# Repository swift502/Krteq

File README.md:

# Krteq

An extended 5x12 keyboard with 2 extra keys. Intended for ortho layouts with a shifted number row, allowing for the placement of the delete and tilde keys above their usual spots.

Krteq is a successor to [Krtkus](https://github.com/swift502/Krtkus), learning from its lessons to make a design that's better encapsulated and much more complete.

### Features

- Low profile
- Hotswap
- RGB backlight
- QMK/VIA compatible
- 3D printed case with a 7 degree tilt
- Tray mount
- 233mm × 121mm × 30mm

Connecting the keyboard to [usevia.app](https://usevia.app) requires manually uploading the [design file](production/krteq_via.json) in the design tab.

## Build guide

### Parts

- [PCB](#pcb)
- [Case](#case)
- Keycaps
- 61x Gateron KS-33 switch
- Gateron 2u low profile plate-mounted stabilizer

<!-- -->

- Raspberry Pi Pico
- USB-C breakout board
- OLED display module

<!-- -->

- 11x connecting wire
- 8x 2,2x8mm thread-forming screws for plastic
- Rubber feet

### Breakout boards

The **USB-C breakout board** is expected to match the specs of the Adafruit USB-C breakout board with two M2.5 screw holes 15.24mm apart, 2.54mm from the front edge, and built-in resistors for the CC lines.

The **OLED display module** is expected to be a 128x32 I2C OLED screen. These screens are not very standardized, so the PCB cutout is generous to fit modules with slightly different dimensions. Any OLED roughly equal or less than 38x12mm should fit, and at most require slight modifications to the display cutout in the plate.

### Assembly

1. Perform the initial firmware flash on the Pico
1. Attach the stabilizer to the plate
1. Place the OLED module into plate's display slot
1. Screw the USB board to the plate
1. Solder the Pico onto the PCB
1. Secure the plate to the PCB by installing few of the switches
1. Cut up wire lenghts:
    - 8x 15mm
    - 2x 18mm (TP2, TP3)
    - 1x 22mm (TP1)
1. Solder the wires to the PCB and the components 
1. Screw the plate to the case
1. Install the rest of the switches, put some keycaps on and you're done!

## PCB

The Kicad 10 project can be found in [source/kicad](source/kicad). All parts are SMD, the PCB is intended to be ordered with pre-assembled SMD components for an easier, although more expensive build process.

To generate fabrication files, open the Kicad project and use an export plugin provided by the PCB manufacturer you want to order from. The order process is then highly dependent on the manufacturer.

### Suggested BOM

| Part | Package | Manufacturer Part Number |
|---|---|---|
| Switch diode | SOD-123 | 1N4148W |
| Switch socket | SMD | KS-2P02B01-02 |
| RGB LED | SMD-4P,3.2x1.3mm | 23-23B/R6GHBHC-A30/2A |
| RGB driver | QFN-48-EP(6x6) | IS31FL3733B-QFLS4-TR |
| 0.1µF capacitor | 0402 | CL05B104KO5NNNC |
| 0.47µF capacitor | 0603 | CL10B474KA8NNNC |
| 22µF/10V capacitor | CASE-A-3216-18(mm) | T520A226M010ATE080 |
| 2kΩ resistor | 0603 | 0603WAF2001T5E |
| 20kΩ resistor | 0603 | 0603WAF2002T5E |
| 100kΩ resistor | 0603 | 0603WAF1003T5E |

## Case

Case blend file can be found in [source/Krteq.blend](source/Krteq.blend). It's designed non-destructively, so it should be easy to modify if needed.

STL files for 3D printing can be found in [production/stl](production/stl). Recommended printing parameters are:

- PLA
- 0.15mm layer height
- 100% infill

The plate also has a "keychron" variant, which adjusts stabilizer cutouts for their non-standard [triangular stem design](https://www.keychron.com/blogs/news/the-design-details-of-our-keychron-low-profile-keyboard-stabilizers).

## Firmware

QMK/VIA setup with a few custom features:

- custom keycodes for volume, screen and RGB control
- pressing <kbd>LShift</kbd> + <kbd>RShift</kbd> + <kbd>Space</kbd> enters bootloader mode
- pressing <kbd>LShift</kbd> + <kbd>RShift</kbd> + <kbd>Delete</kbd> reverts to the default keymap

### Overrides

Some functionality can be overridden in a user keymap `config.h`:

```c
// Replace the scroll lock indicator with three letter
// string to denote custom script functionality
#define INDICATORS_SCROLL_LABEL "ACC"

// Layer which forces a preview of the "Indicators" screen
#define INDICATORS_SHOW_LAYER 1

// Layer (and above) which shows the "Input lock" screen
#define INPUT_LOCK_LAYER 4

```

### Adding custom OLED screens

In QMK, user keymaps can completely override oled rendering via `oled_task_user()`. However, Krteq also exposes its custom screen system, where screen interaction is done via the `KRT_SCR` keycode. Hooking into this system is preferred as it ensures that other built-in system screen features continue to work properly.

Here's a minimal example of a custom screen definition in a user keymap:

```c
// 1. Create a render function
static void custom_screen_render(void)
{
    oled_write_P(PSTR("Hello world"), false);
}

// 2. Construct a screen instance
static const krteq_screen_t custom_screen = {
    .name = "Custom screen",
    .start = custom_screen_render,
};

// 3. Override built-in screen list
const krteq_screen_t *const user_screens[] = {
    &custom_screen
};
```

Here's a table of fields and callbacks available for screens to implement:

| Property     | Description |
| ------------ | ----------- |
| `.name`      | Display name string |
| `.init`      | Runs once on keyboard start-up |
| `.start`     | Runs every time the screen is activated |
| `.update`    | Runs every OLED task cycle when screen is active |
| `.key_event` | Key press event |

You can combine custom screens with the built-in ones. You can reshuffle them, remove some and add your own. The built-in screen list goes as follows:

```c
const krteq_screen_t *const user_screens[] = {
    &krteq_screen_indicators,
    &krteq_screen_bongo_cat,
    &krteq_screen_starfield,
    &krteq_screen_matrix,
    &krteq_screen_waves,
    &krteq_screen_game_of_life,
    &krteq_screen_system_info
};
```

### Compiling (Windows)

Install:

- Python: https://www.python.org/
- MSYS: https://msys.qmk.fm

Run the compile script:

```sh
python source/scripts/qmk_compile.py
```

### Flashing (Windows)

For the initial flash, hold the BOOTSEL button while connecting the Pico to a computer to have it show up as a storage device, then copy the compiled [firmware file](production/krteq_firmware.uf2) over to it.

Once flashed, you can trigger the bootloader mode again by simply pressing the <kbd>LShift</kbd> + <kbd>RShift</kbd> + <kbd>Space</kbd> key combination.

## Documentation

### QMK

- Info.json: https://docs.qmk.fm/reference_info_json
- Keycodes: https://docs.qmk.fm/keycodes
- Default keymap: https://docs.qmk.fm/configurator_default_keymaps
- RGB matrix: https://docs.qmk.fm/features/rgb_matrix
- OLED: https://docs.qmk.fm/features/oled_driver

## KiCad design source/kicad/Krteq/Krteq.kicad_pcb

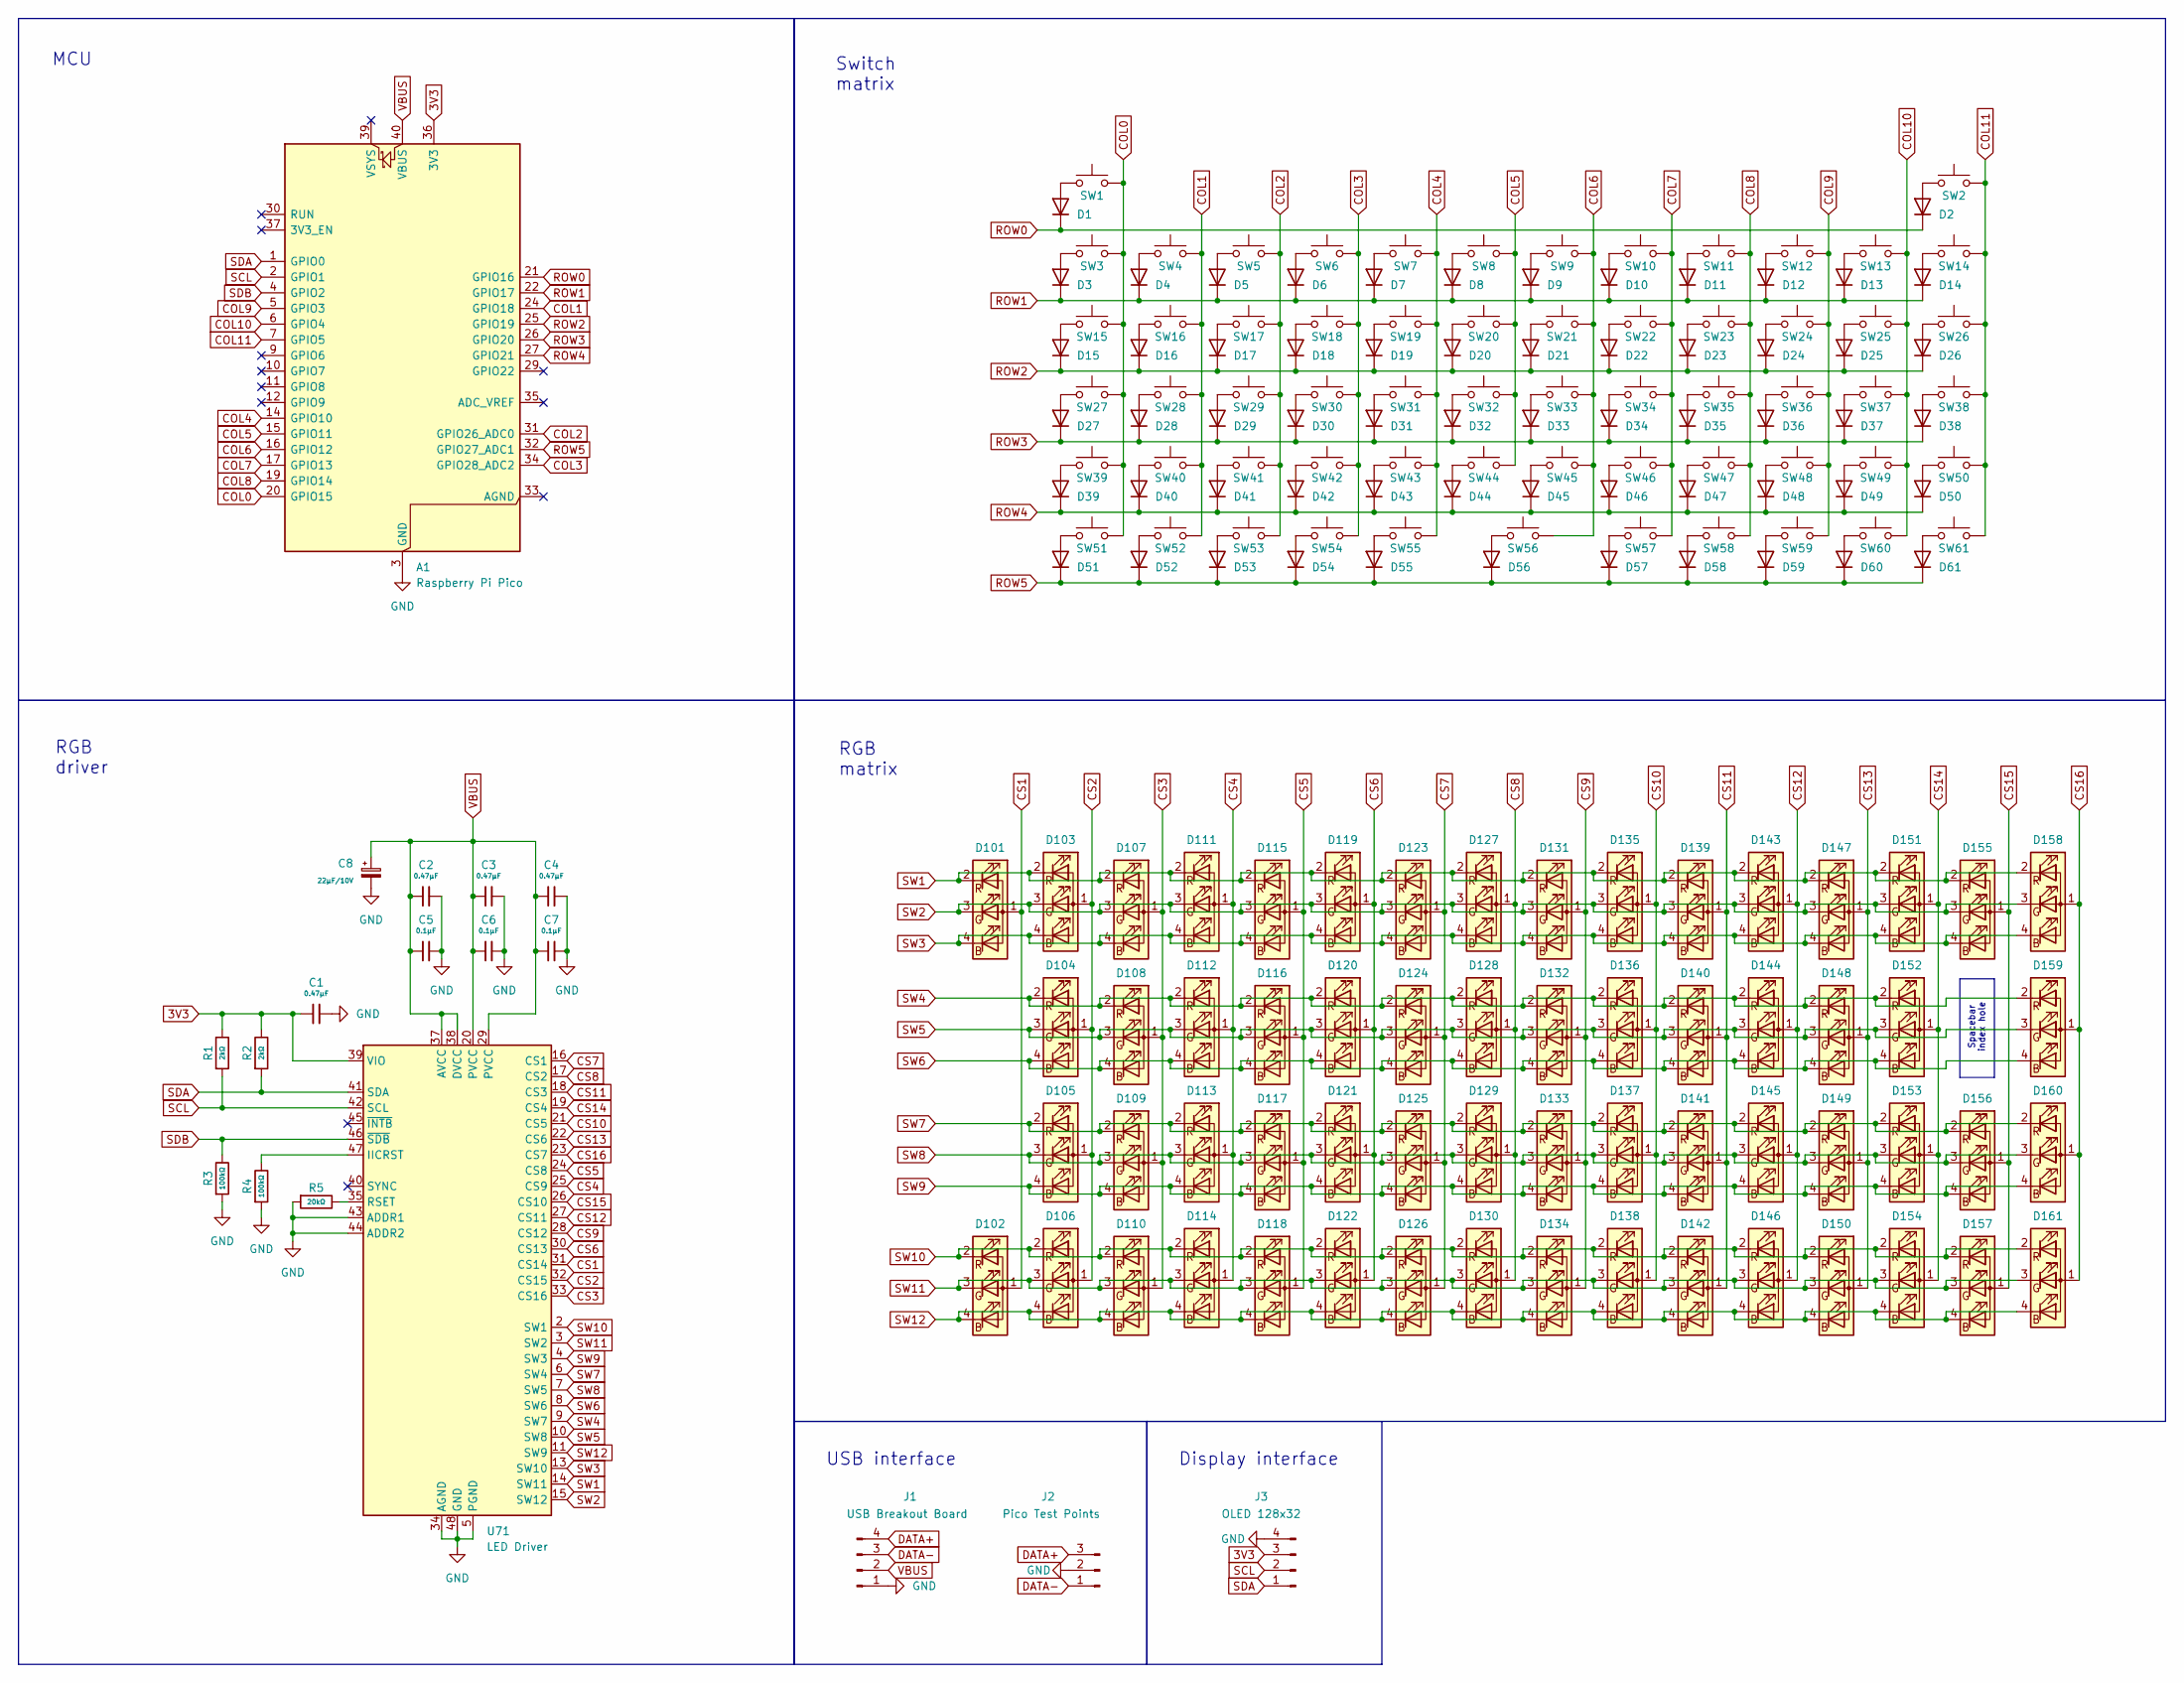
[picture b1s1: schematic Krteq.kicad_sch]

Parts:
A1: Raspberry Pi Pico; RaspberryPi_Pico
C1, C2, C3, C4: 0.47µF; C_0603_1608Metric; MPN CL10B474KA8NNNC
C5, C6, C7: 0.1µF; C_0402_1005Metric; MPN CL05B104KO5NNNC
C8: 22µF/10V; CASE-A-3216-18(mm); MPN T520A226M010ATE080
D1, D2, D3, D4, D5, D6, D7, D8, D9, D10, D11, D12, D13, D14, D15, D16, D17, D18, D19, D20, D21, D22, D23, D24, D25, D26, D27, D28, D29, D30, D31, D32, D33, D34, D35, D36, D37, D38, D39, D40, D41, D42, D43, D44, D45, D46, D47, D48, D49, D50, D51, D52, D53, D54, D55, D56, D57, D58, D59, D60, D61: Switch Diode; D_SOD-123; MPN 1N4148W
D101, D102, D103, D104, D105, D106, D107, D108, D109, D110, D111, D112, D113, D114, D115, D116, D117, D118, D119, D120, D121, D122, D123, D124, D125, D126, D127, D128, D129, D130, D131, D132, D133, D134, D135, D136, D137, D138, D139, D140, D141, D142, D143, D144, D145, D146, D147, D148, D149, D150, D151, D152, D153, D154, D155, D156, D157, D158, D159, D160, D161: Reverse Mount LED ARGB; SMD-4P_3.2x1.3mm; MPN 23-23B/R6GHBHC-A30/2A
J1: USB Breakout Board; Interface_1x04_P2.54mm
J2: Pico Test Points; Interface_1x03_P2.54mm
J3: OLED 128x32; Interface_1x04_P2.54mm
R1, R2: 2kΩ; R_0603_1608Metric; MPN 0603WAF2001T5E
R3, R4: 100kΩ; R_0603_1608Metric; MPN 0603WAF1003T5E
R5: 20kΩ; R_0603_1608Metric; MPN 0603WAF2002T5E
SW1, SW2, SW3, SW4, SW5, SW6, SW7, SW8, SW9, SW10, SW11, SW12, SW13, SW14, SW15, SW16, SW17, SW18, SW19, SW20, SW21, SW22, SW23, SW24, SW25, SW26, SW27, SW28, SW29, SW30, SW31, SW32, SW33, SW34, SW35, SW36, SW37, SW38, SW39, SW40, SW41, SW42, SW43, SW44, SW45, SW46, SW47, SW48, SW49, SW50, SW51, SW52, SW53, SW54, SW55, SW56, SW57, SW58, SW59, SW60, SW61: GATERON Low Profile Switch Hot-swap Socket; Gateron_KS-33; MPN KS-2P02B01-02
U71: LED Driver; QFN-48_6x6mm; MPN IS31FL3733B-QFLS4-TR

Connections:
3V3: A1.36 (3V3), C1.1, J3.3, R1.1, R2.1, U71.39 (VIO)
COL0: A1.20 (GPIO15), SW1.2, SW3.2, SW15.2, SW27.2, SW39.2, SW51.2
COL1: A1.24 (GPIO18), SW4.2, SW16.2, SW28.2, SW40.2, SW52.2
COL2: A1.31 (GPIO26_ADC0), SW5.2, SW17.2, SW29.2, SW41.2, SW53.2
COL3: A1.34 (GPIO28_ADC2), SW6.2, SW18.2, SW30.2, SW42.2, SW54.2
COL4: A1.14 (GPIO10), SW7.2, SW19.2, SW31.2, SW43.2, SW55.2
COL5: A1.15 (GPIO11), SW8.2, SW20.2, SW32.2, SW44.2
COL6: A1.16 (GPIO12), SW9.2, SW21.2, SW33.2, SW45.2, SW56.2
COL7: A1.17 (GPIO13), SW10.2, SW22.2, SW34.2, SW46.2, SW57.2
COL8: A1.19 (GPIO14), SW11.2, SW23.2, SW35.2, SW47.2, SW58.2
COL9: A1.5 (GPIO3), SW12.2, SW24.2, SW36.2, SW48.2, SW59.2
COL10: A1.6 (GPIO4), SW13.2, SW25.2, SW37.2, SW49.2, SW60.2
COL11: A1.7 (GPIO5), SW2.2, SW14.2, SW26.2, SW38.2, SW50.2, SW61.2
CS1: D101.1 (A), D102.1 (A), U71.31 (CS14)
CS2: D103.1 (A), D104.1 (A), D105.1 (A), D106.1 (A), U71.32 (CS15)
CS3: D107.1 (A), D108.1 (A), D109.1 (A), D110.1 (A), U71.33 (CS16)
CS4: D111.1 (A), D112.1 (A), D113.1 (A), D114.1 (A), U71.25 (CS9)
CS5: D115.1 (A), D116.1 (A), D117.1 (A), D118.1 (A), U71.24 (CS8)
CS6: D119.1 (A), D120.1 (A), D121.1 (A), D122.1 (A), U71.30 (CS13)
CS7: D123.1 (A), D124.1 (A), D125.1 (A), D126.1 (A), U71.16 (CS1)
CS8: D127.1 (A), D128.1 (A), D129.1 (A), D130.1 (A), U71.17 (CS2)
CS9: D131.1 (A), D132.1 (A), D133.1 (A), D134.1 (A), U71.28 (CS12)
CS10: D135.1 (A), D136.1 (A), D137.1 (A), D138.1 (A), U71.21 (CS5)
CS11: D139.1 (A), D140.1 (A), D141.1 (A), D142.1 (A), U71.18 (CS3)
CS12: D143.1 (A), D144.1 (A), D145.1 (A), D146.1 (A), U71.27 (CS11)
CS13: D147.1 (A), D148.1 (A), D149.1 (A), D150.1 (A), U71.22 (CS6)
CS14: D151.1 (A), D152.1 (A), D153.1 (A), D154.1 (A), U71.19 (CS4)
CS15: D155.1 (A), D156.1 (A), D157.1 (A), U71.26 (CS10)
CS16: D158.1 (A), D159.1 (A), D160.1 (A), D161.1 (A), U71.23 (CS7)
DATA+: J1.4, J2.3
DATA-: J1.3, J2.1
GND: A1.3 (GND), A1.8 (GND), A1.13 (GND), A1.18 (GND), A1.23 (GND), A1.28 (GND), A1.38 (GND), C1.2, C2.2, C3.2, C4.2, C5.2, C6.2, C7.2, C8.2, J1.1, J2.2, J3.4, R3.2, R4.2, R5.2, U71.5 (PGND), U71.12 (PGND), U71.34 (AGND), U71.43 (ADDR1), U71.44 (ADDR2), U71.48 (GND), U71.49 (GND)
unnamed: D1.2 (A), SW1.1
unnamed: D2.2 (A), SW2.1
unnamed: D3.2 (A), SW3.1
unnamed: D4.2 (A), SW4.1
unnamed: D5.2 (A), SW5.1
unnamed: D6.2 (A), SW6.1
unnamed: D7.2 (A), SW7.1
unnamed: D8.2 (A), SW8.1
unnamed: D9.2 (A), SW9.1
unnamed: D10.2 (A), SW10.1
unnamed: D11.2 (A), SW11.1
unnamed: D12.2 (A), SW12.1
unnamed: D13.2 (A), SW13.1
unnamed: D14.2 (A), SW14.1
unnamed: D15.2 (A), SW15.1
unnamed: D16.2 (A), SW16.1
unnamed: D17.2 (A), SW17.1
unnamed: D18.2 (A), SW18.1
unnamed: D19.2 (A), SW19.1
unnamed: D20.2 (A), SW20.1
unnamed: D21.2 (A), SW21.1
unnamed: D22.2 (A), SW22.1
unnamed: D23.2 (A), SW23.1
unnamed: D24.2 (A), SW24.1
unnamed: D25.2 (A), SW25.1
unnamed: D26.2 (A), SW26.1
unnamed: D27.2 (A), SW27.1
unnamed: D28.2 (A), SW28.1
unnamed: D29.2 (A), SW29.1
unnamed: D30.2 (A), SW30.1
unnamed: D31.2 (A), SW31.1
unnamed: D32.2 (A), SW32.1
unnamed: D33.2 (A), SW33.1
unnamed: D34.2 (A), SW34.1
unnamed: D35.2 (A), SW35.1
unnamed: D36.2 (A), SW36.1
unnamed: D37.2 (A), SW37.1
unnamed: D38.2 (A), SW38.1
unnamed: D39.2 (A), SW39.1
unnamed: D40.2 (A), SW40.1
unnamed: D41.2 (A), SW41.1
unnamed: D42.2 (A), SW42.1
unnamed: D43.2 (A), SW43.1
unnamed: D44.2 (A), SW44.1
unnamed: D45.2 (A), SW45.1
unnamed: D46.2 (A), SW46.1
unnamed: D47.2 (A), SW47.1
unnamed: D48.2 (A), SW48.1
unnamed: D49.2 (A), SW49.1
unnamed: D50.2 (A), SW50.1
unnamed: D51.2 (A), SW51.1
unnamed: D52.2 (A), SW52.1
unnamed: D53.2 (A), SW53.1
unnamed: D54.2 (A), SW54.1
unnamed: D55.2 (A), SW55.1
unnamed: D56.2 (A), SW56.1
unnamed: D57.2 (A), SW57.1
unnamed: D58.2 (A), SW58.1
unnamed: D59.2 (A), SW59.1
unnamed: D60.2 (A), SW60.1
unnamed: D61.2 (A), SW61.1
unnamed: R4.1, U71.47 (IICRST)
unnamed: R5.1, U71.35 (RSET)
ROW0: A1.21 (GPIO16), D1.1 (K), D2.1 (K)
ROW1: A1.22 (GPIO17), D3.1 (K), D4.1 (K), D5.1 (K), D6.1 (K), D7.1 (K), D8.1 (K), D9.1 (K), D10.1 (K), D11.1 (K), D12.1 (K), D13.1 (K), D14.1 (K)
ROW2: A1.25 (GPIO19), D15.1 (K), D16.1 (K), D17.1 (K), D18.1 (K), D19.1 (K), D20.1 (K), D21.1 (K), D22.1 (K), D23.1 (K), D24.1 (K), D25.1 (K), D26.1 (K)
ROW3: A1.26 (GPIO20), D27.1 (K), D28.1 (K), D29.1 (K), D30.1 (K), D31.1 (K), D32.1 (K), D33.1 (K), D34.1 (K), D35.1 (K), D36.1 (K), D37.1 (K), D38.1 (K)
ROW4: A1.27 (GPIO21), D39.1 (K), D40.1 (K), D41.1 (K), D42.1 (K), D43.1 (K), D44.1 (K), D45.1 (K), D46.1 (K), D47.1 (K), D48.1 (K), D49.1 (K), D50.1 (K)
ROW5: A1.32 (GPIO27_ADC1), D51.1 (K), D52.1 (K), D53.1 (K), D54.1 (K), D55.1 (K), D56.1 (K), D57.1 (K), D58.1 (K), D59.1 (K), D60.1 (K), D61.1 (K)
SCL: A1.2 (GPIO1), J3.2, R1.2, U71.42 (SCL)
SDA: A1.1 (GPIO0), J3.1, R2.2, U71.41 (SDA)
SDB: A1.4 (GPIO2), R3.1, U71.46 (~SDB)
SW1: D101.2 (RK), D103.2 (RK), D107.2 (RK), D111.2 (RK), D115.2 (RK), D119.2 (RK), D123.2 (RK), D127.2 (RK), D131.2 (RK), D135.2 (RK), D139.2 (RK), D143.2 (RK), D147.2 (RK), D151.2 (RK), D155.2 (RK), D158.2 (RK), U71.14 (SW11)
SW2: D101.3 (GK), D103.3 (GK), D107.3 (GK), D111.3 (GK), D115.3 (GK), D119.3 (GK), D123.3 (GK), D127.3 (GK), D131.3 (GK), D135.3 (GK), D139.3 (GK), D143.3 (GK), D147.3 (GK), D151.3 (GK), D155.3 (GK), D158.3 (GK), U71.15 (SW12)
SW3: D101.4 (BK), D103.4 (BK), D107.4 (BK), D111.4 (BK), D115.4 (BK), D119.4 (BK), D123.4 (BK), D127.4 (BK), D131.4 (BK), D135.4 (BK), D139.4 (BK), D143.4 (BK), D147.4 (BK), D151.4 (BK), D155.4 (BK), D158.4 (BK), U71.13 (SW10)
SW4: D104.2 (RK), D108.2 (RK), D112.2 (RK), D116.2 (RK), D120.2 (RK), D124.2 (RK), D128.2 (RK), D132.2 (RK), D136.2 (RK), D140.2 (RK), D144.2 (RK), D148.2 (RK), D152.2 (RK), D159.2 (RK), U71.9 (SW7)
SW5: D104.3 (GK), D108.3 (GK), D112.3 (GK), D116.3 (GK), D120.3 (GK), D124.3 (GK), D128.3 (GK), D132.3 (GK), D136.3 (GK), D140.3 (GK), D144.3 (GK), D148.3 (GK), D152.3 (GK), D159.3 (GK), U71.10 (SW8)
SW6: D104.4 (BK), D108.4 (BK), D112.4 (BK), D116.4 (BK), D120.4 (BK), D124.4 (BK), D128.4 (BK), D132.4 (BK), D136.4 (BK), D140.4 (BK), D144.4 (BK), D148.4 (BK), D152.4 (BK), D159.4 (BK), U71.8 (SW6)
SW7: D105.2 (RK), D109.2 (RK), D113.2 (RK), D117.2 (RK), D121.2 (RK), D125.2 (RK), D129.2 (RK), D133.2 (RK), D137.2 (RK), D141.2 (RK), D145.2 (RK), D149.2 (RK), D153.2 (RK), D156.2 (RK), D160.2 (RK), U71.6 (SW4)
SW8: D105.3 (GK), D109.3 (GK), D113.3 (GK), D117.3 (GK), D121.3 (GK), D125.3 (GK), D129.3 (GK), D133.3 (GK), D137.3 (GK), D141.3 (GK), D145.3 (GK), D149.3 (GK), D153.3 (GK), D156.3 (GK), D160.3 (GK), U71.7 (SW5)
SW9: D105.4 (BK), D109.4 (BK), D113.4 (BK), D117.4 (BK), D121.4 (BK), D125.4 (BK), D129.4 (BK), D133.4 (BK), D137.4 (BK), D141.4 (BK), D145.4 (BK), D149.4 (BK), D153.4 (BK), D156.4 (BK), D160.4 (BK), U71.4 (SW3)
SW10: D102.2 (RK), D106.2 (RK), D110.2 (RK), D114.2 (RK), D118.2 (RK), D122.2 (RK), D126.2 (RK), D130.2 (RK), D134.2 (RK), D138.2 (RK), D142.2 (RK), D146.2 (RK), D150.2 (RK), D154.2 (RK), D157.2 (RK), D161.2 (RK), U71.2 (SW1)
SW11: D102.3 (GK), D106.3 (GK), D110.3 (GK), D114.3 (GK), D118.3 (GK), D122.3 (GK), D126.3 (GK), D130.3 (GK), D134.3 (GK), D138.3 (GK), D142.3 (GK), D146.3 (GK), D150.3 (GK), D154.3 (GK), D157.3 (GK), D161.3 (GK), U71.3 (SW2)
SW12: D102.4 (BK), D106.4 (BK), D110.4 (BK), D114.4 (BK), D118.4 (BK), D122.4 (BK), D126.4 (BK), D130.4 (BK), D134.4 (BK), D138.4 (BK), D142.4 (BK), D146.4 (BK), D150.4 (BK), D154.4 (BK), D157.4 (BK), D161.4 (BK), U71.11 (SW9)
VBUS: A1.40 (VBUS), C2.1, C3.1, C4.1, C5.1, C6.1, C7.1, C8.1, J1.2, U71.20 (PVCC), U71.29 (PVCC), U71.37 (AVCC), U71.38 (DVCC)

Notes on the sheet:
RGB matrix
Switch matrix
RGB driver
USB interface
Spacebar index hole
MCU
Display interface

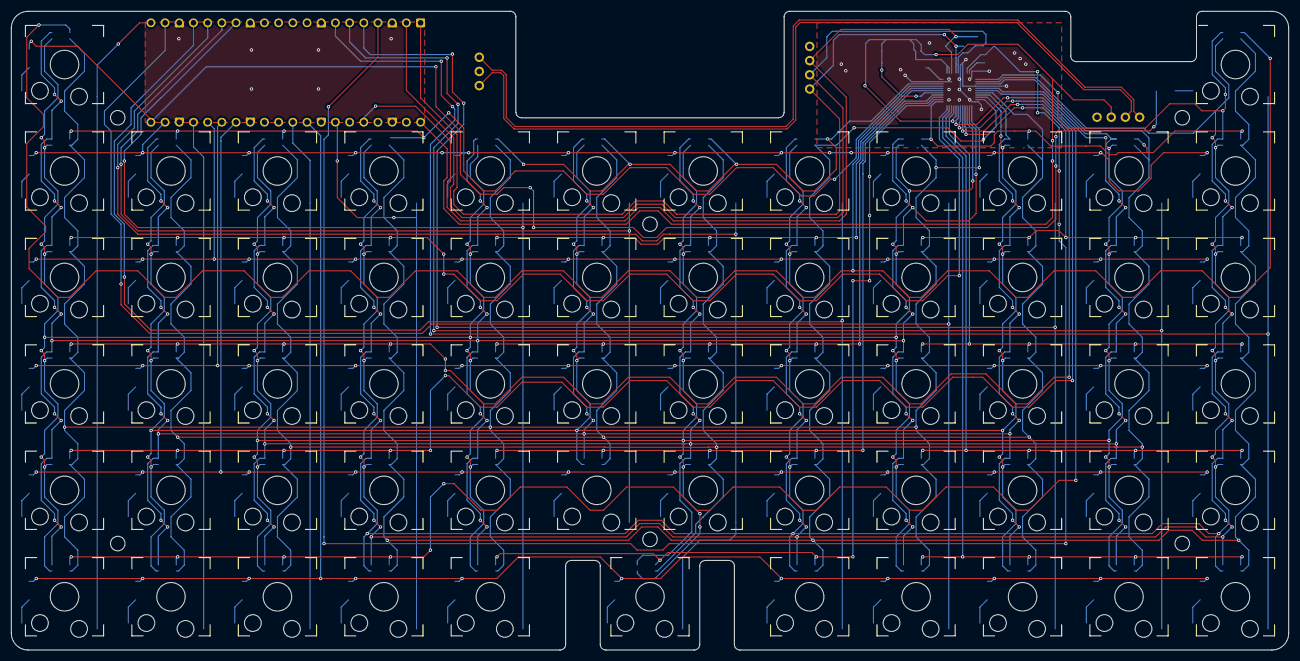
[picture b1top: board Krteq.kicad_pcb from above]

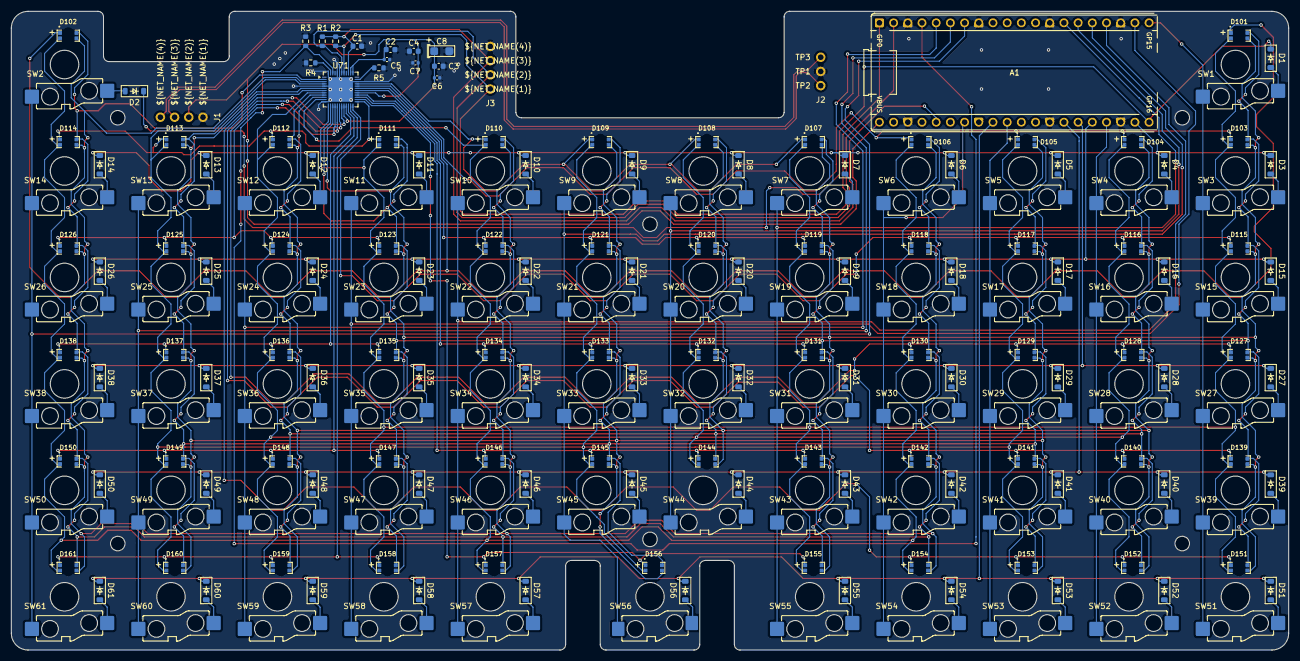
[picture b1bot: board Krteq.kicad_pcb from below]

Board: 2 copper layers, 228.6 x 114.3 mm, 201 parts (201 on the bottom side), 117 nets.

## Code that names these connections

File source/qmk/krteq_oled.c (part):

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
// Drawn as rows top to bottom, 3 bits each, the leftmost pixel in the highest bit
// Stored as columns left to right, 4 bits each, the top pixel in the lowest bit, which the frame buffer takes directly
#define RAIN_GLYPH_COLUMN(row0, row1, row2, row3, bit) \
    (((row0) >> (bit) & 1) | ((row1) >> (bit) & 1) << 1 | ((row2) >> (bit) & 1) << 2 | ((row3) >> (bit) & 1) << 3)
#define RAIN_GLYPH(row0, row1, row2, row3) \
    (RAIN_GLYPH_COLUMN(row0, row1, row2, row3, 2) | RAIN_GLYPH_COLUMN(row0, row1, row2, row3, 1) << 4 | RAIN_GLYPH_COLUMN(row0, row1, row2, row3, 0) << 8)

// Katakana, digits and punctuation, 8 to 11 pixels
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
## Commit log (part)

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2026-05-02 video link
2026-05-02 video link 2
2026-05-02 readme
2026-06-02 note for msys update
